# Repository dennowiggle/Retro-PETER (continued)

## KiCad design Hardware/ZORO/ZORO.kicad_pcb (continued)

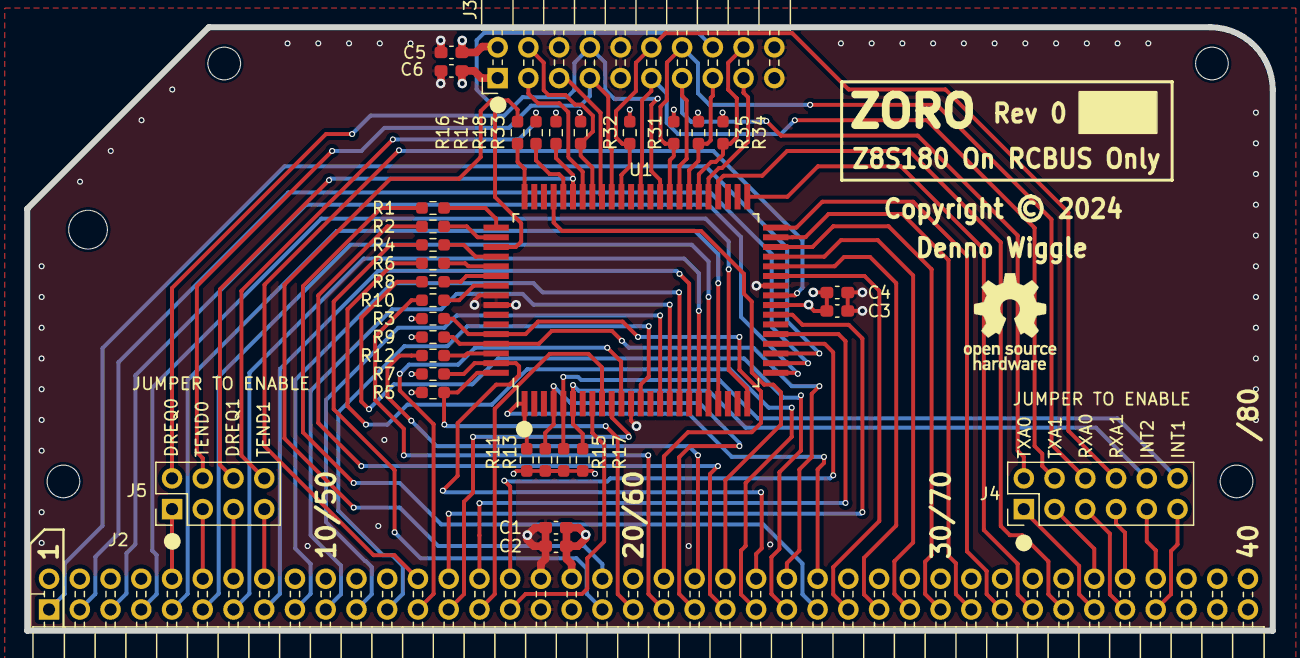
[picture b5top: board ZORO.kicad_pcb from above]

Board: 4 copper layers, 102.9 x 49.9 mm, 41 parts (1 on the bottom side), 81 nets.

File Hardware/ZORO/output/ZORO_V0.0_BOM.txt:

"Reference","Value","Footprint","Qty","DNP","Digikey","Footprint2","LCSC Part #","MPN","Description"
"U1","Z8S18020FSG","WTM_Library:PQFP-80_14x20mm_P0.8mm","1","","269-4541-5-ND","","","Z8S18020FSG","Z8S180 Microprocessor IC Z180 1 Core, 8-Bit 20MHz 80-QFP"
"J2","Conn_02x40_Top_Bottom","WTM_Library:RCBUS_PinHeader_2x40_P2.54mm_Horizontal","1","","A34274-40-ND","","","9-103795-0","CONN HEADER R/A 80POS 2.54MM"
"J3","Conn_02x10_Odd_Even","Connector_PinHeader_2.54mm:PinHeader_2x10_P2.54mm_Horizontal","1","","2057-PH2RA-20-UA-ND","","","PH2RA-20-UA","CONN HEADER HORIZONTAL 20POS 2.54MM"
"J4","Conn_02x06_Odd_Even","Connector_PinHeader_2.54mm:PinHeader_2x06_P2.54mm_Vertical","1","","2057-PH2-12-UA-ND","","","PH2-12-UA","CONN HEADER VERT 12POS 2.54MM"
"J5","Conn_02x04_Odd_Even","Connector_PinHeader_2.54mm:PinHeader_2x04_P2.54mm_Vertical","1","","2057-PH2-08-UA-ND","","","PH2-08-UA","CONN HEADER VERT 8POS 2.54MM"
"R3,R5,R7,R9,R11,R13,R15,R17,R18,R31,R32,R33,R34,R35","10K","Resistor_SMD:R_0603_1608Metric_Pad0.98x0.95mm_HandSolder","14","","311-10.0KHRCT-ND","0603H","C98220","RC0603FR-0710KL","RES 10K OHM 1% 1/10W 0603"
"R1,R2,R4,R6,R8,R10,R12,R14,R16","33R","Resistor_SMD:R_0603_1608Metric_Pad0.98x0.95mm_HandSolder","9","","13-RC0603FR-0733RLCT-ND","0603H","C108661","RC0603FR-0733RL","RES 33 OHM 1% 1/10W 0603"
"C1,C3,C5","4.7uF","Capacitor_SMD:C_0603_1608Metric_Pad1.08x0.95mm_HandSolder","3","","1276-1784-1-ND","0603H","C19666","CL10A475KO8NNNC","CAP CER 4.7UF 16V X5R 0603"
"C2,C4,C6","100nF","Capacitor_SMD:C_0603_1608Metric_Pad1.08x0.95mm_HandSolder","3","","311-1344-1-ND","0603H","C14663","CC0603KRX7R9BB104","CAP CER 0.1UF 50V X7R 0603"

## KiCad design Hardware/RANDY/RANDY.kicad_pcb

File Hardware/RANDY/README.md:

# RANDY
RCBUS Adapter to Nouveau Design. Yeah!

## Description
This project is an adapter board to interface the [2067-Z8S180 board](https://github.com/johnwinans/2067-Z8S180) from John Winan's Z80 Nouveau Project to an RCBUS backplane board connector. 
* If a right-angle RCBUS socket is installed on the top side, the board will plug into an RCBUS expansion port.
* If a right-angle RCBUS plug is installed on the bottom side, the board will plug into an RCBUS card slot.

## Top View

## Bottom View

## RANDY Board Rev 0.0 Release Notes

1. The 'output' directory contains the BOM, netlist, and PDF schematic.

2. Board design used KiCad 8.0.4.

3. J2 changed to Samtec SSW-140-02-F-D-RA.

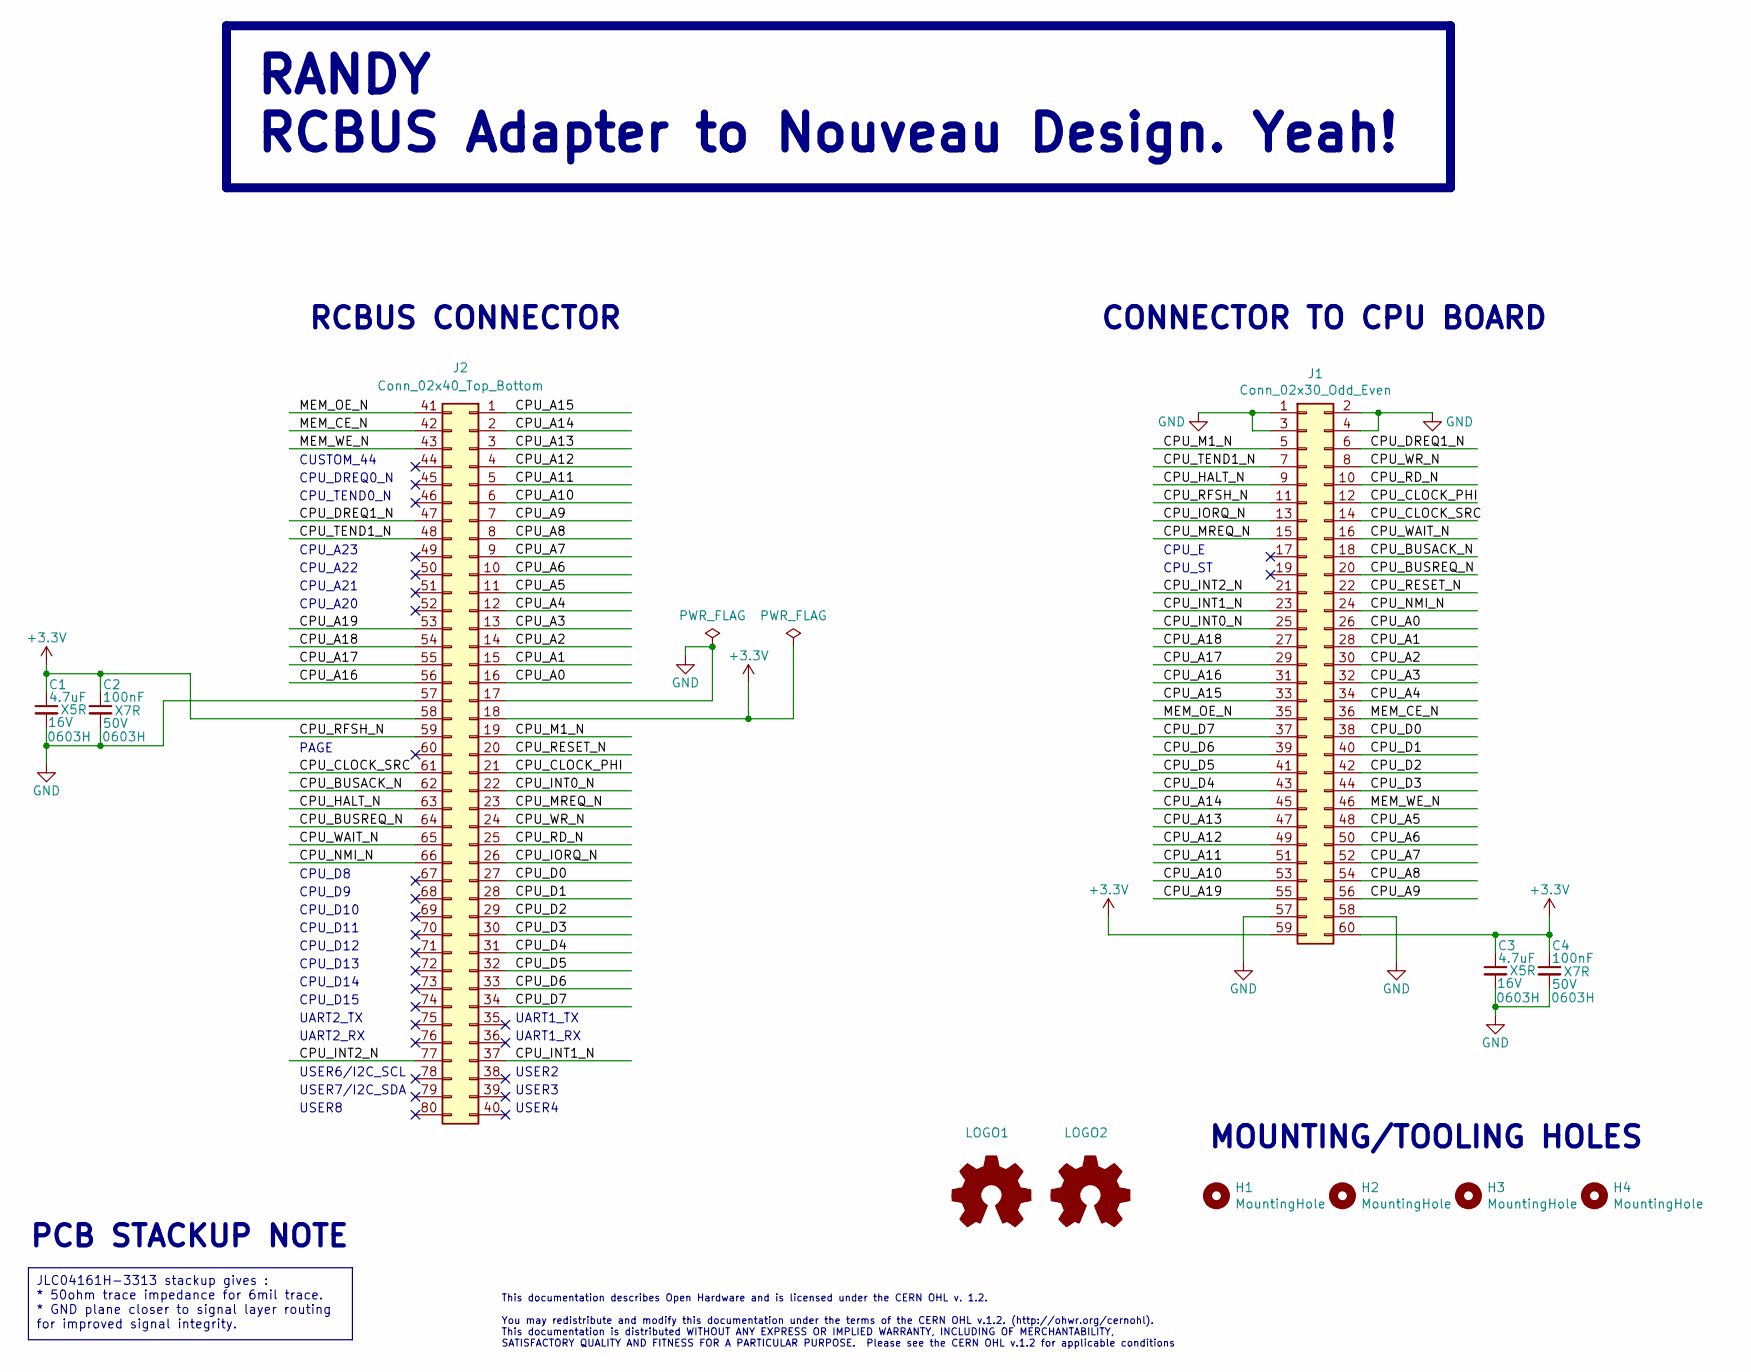
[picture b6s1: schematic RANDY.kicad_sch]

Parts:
C1, C3: 4.7uF; C_0603_1608Metric_Pad1.08x0.95mm_HandSolder; Voltage 16V; Tolerance 10%; MPN CL10A475KO8NNNC; Digikey 1276-1784-1-ND
C2, C4: 100nF; C_0603_1608Metric_Pad1.08x0.95mm_HandSolder; Voltage 50V; Tolerance 10%; MPN CC0603KRX7R9BB104; Digikey 311-1344-1-ND
H1, H2, H3, H4: MountingHole; MountingHole_2.7mm_M2.5_DIN965
J1: Conn_02x30_Odd_Even; PinHeader_2x30_P2.54mm_Vertical; MPN 67996-160HLF; Digikey 609-6334-ND
J2: Conn_02x40_Top_Bottom; PinSocket_2x40_P2.54mm_Horizontal_RCBUS80; MPN SSW-140-02-T-D-RA; Digikey 612-SSW-140-02-T-D-RA-ND
LOGO1, LOGO2: Logo_Open_Hardware_Small; OSHW-Logo_7.5x8mm_SilkScreen

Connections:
+3.3V: C1.1, C2.1, C3.1, C4.1, J1.59, J1.60, J2.18, J2.58
/CPU_A0: J1.26, J2.16
/CPU_A1: J1.28, J2.15
/CPU_A2: J1.30, J2.14
/CPU_A3: J1.32, J2.13
/CPU_A4: J1.34, J2.12
/CPU_A5: J1.48, J2.11
/CPU_A6: J1.50, J2.10
/CPU_A7: J1.52, J2.9
/CPU_A8: J1.54, J2.8
/CPU_A9: J1.56, J2.7
/CPU_A10: J1.53, J2.6
/CPU_A11: J1.51, J2.5
/CPU_A12: J1.49, J2.4
/CPU_A13: J1.47, J2.3
/CPU_A14: J1.45, J2.2
/CPU_A15: J1.33, J2.1
/CPU_A16: J1.31, J2.56
/CPU_A17: J1.29, J2.55
/CPU_A18: J1.27, J2.54
/CPU_A19: J1.55, J2.53
/CPU_BUSACK_N: J1.18, J2.62
/CPU_BUSREQ_N: J1.20, J2.64
/CPU_CLOCK_PHI: J1.12, J2.21
/CPU_CLOCK_SRC: J1.14, J2.61
/CPU_D0: J1.38, J2.27
/CPU_D1: J1.40, J2.28
/CPU_D2: J1.42, J2.29
/CPU_D3: J1.44, J2.30
/CPU_D4: J1.43, J2.31
/CPU_D5: J1.41, J2.32
/CPU_D6: J1.39, J2.33
/CPU_D7: J1.37, J2.34
/CPU_DREQ1_N: J1.6, J2.47
/CPU_HALT_N: J1.9, J2.63
/CPU_INT0_N: J1.25, J2.22
/CPU_INT1_N: J1.23, J2.37
/CPU_INT2_N: J1.21, J2.77
/CPU_IORQ_N: J1.13, J2.26
/CPU_M1_N: J1.5, J2.19
/CPU_MREQ_N: J1.15, J2.23
/CPU_NMI_N: J1.24, J2.66
/CPU_RD_N: J1.10, J2.25
/CPU_RESET_N: J1.22, J2.20
/CPU_RFSH_N: J1.11, J2.59
/CPU_TEND1_N: J1.7, J2.48
/CPU_WAIT_N: J1.16, J2.65
/CPU_WR_N: J1.8, J2.24
/MEM_CE_N: J1.36, J2.42
/MEM_OE_N: J1.35, J2.41
/MEM_WE_N: J1.46, J2.43
GND: C1.2, C2.2, C3.2, C4.2, J1.1, J1.2, J1.3, J1.4, J1.57, J1.58, J2.17, J2.57

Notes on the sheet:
RANDY RCBUS Adapter to Nouveau Design. Yeah!
JLC04161H-3313 stackup gives : * 50ohm trace impedance for 6mil trace. * GND plane closer to signal layer routing for improved signal integrity.
UART1_TX
MOUNTING/TOOLING HOLES
CPU_ST
CONNECTOR TO CPU BOARD
CPU_A22
USER4
CPU_TEND0_N
CPU_D8
CPU_A21
CPU_D11
UART2_RX
CPU_D13
CUSTOM_44
USER6/I2C_SCL
CPU_A23
CPU_D12
PCB STACKUP NOTE
USER8
CPU_E
CPU_D10
CPU_D9
CPU_A20
UART2_TX
CPU_D14
USER3
PAGE
USER2
RCBUS CONNECTOR
CPU_DREQ0_N
This documentation describes Open Hardware and is licensed under the CERN OHL v. 1.2. You may redistribute and modify this documentation under the terms of the CERN OHL v.1.2. (http://ohwr.org/cernohl). This documentation is distributed WITHOUT ANY EXPRESS OR IMPLIED WARRANTY, INCLUDING OF MERCHANT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
USER7/I2C_SDA
CPU_D15
UART1_RX

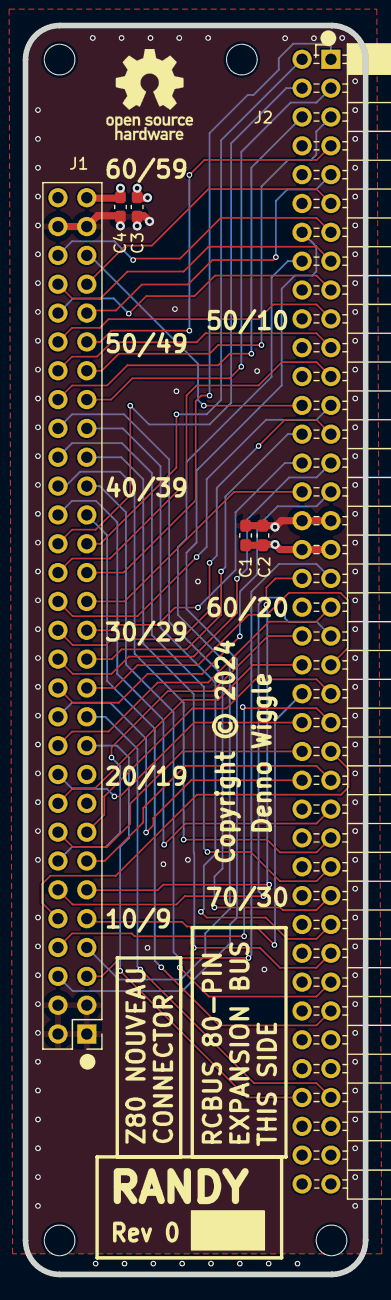
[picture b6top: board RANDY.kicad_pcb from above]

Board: 4 copper layers, 30.0 x 110.0 mm, 12 parts (1 on the bottom side), 52 nets.

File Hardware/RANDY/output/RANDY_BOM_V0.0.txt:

"Reference","Value","Footprint","Qty","DNP","Digikey","LCSC Part #","MPN","Voltage","Description"
"C2,C4","100nF","Capacitor_SMD:C_0603_1608Metric_Pad1.08x0.95mm_HandSolder","2","","311-1344-1-ND","C14663","CC0603KRX7R9BB104","50V","CAP CER 0.1UF 50V X7R 0603"
"C1,C3","4.7uF","Capacitor_SMD:C_0603_1608Metric_Pad1.08x0.95mm_HandSolder","2","","1276-1784-1-ND","C19666","CL10A475KO8NNNC","16V","CAP CER 4.7UF 16V X5R 0603"
"J1","Conn_02x30_Odd_Even","Connector_PinHeader_2.54mm:PinHeader_2x30_P2.54mm_Vertical","1","","609-6334-ND","","67996-160HLF","","CONN HEADER VERT 60POS 2.54MM"
"J2","Conn_02x40_Top_Bottom","WTM_Library:PinSocket_2x40_P2.54mm_Horizontal_RCBUS80","1","","612-SSW-140-02-T-D-RA-ND","","SSW-140-02-T-D-RA","","CONN RCPT 80POS 0.1 TIN PCB R/A"

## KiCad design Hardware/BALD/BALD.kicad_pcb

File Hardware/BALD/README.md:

# BALD
Bus Activity LED Display.

## Description
BALD is an RCBUS board with LED's to show bus activity.

## Top View

## Bottom View

## BALD Board Rev 0.0 Release Notes

1. The 'output' directory contains the BOM, netlist, and PDF schematic.

2. Board design used KiCad 8.0.4.

3. J1 was changed to Adam Tech part number PH2RA-80-UA to reduce insertion force.

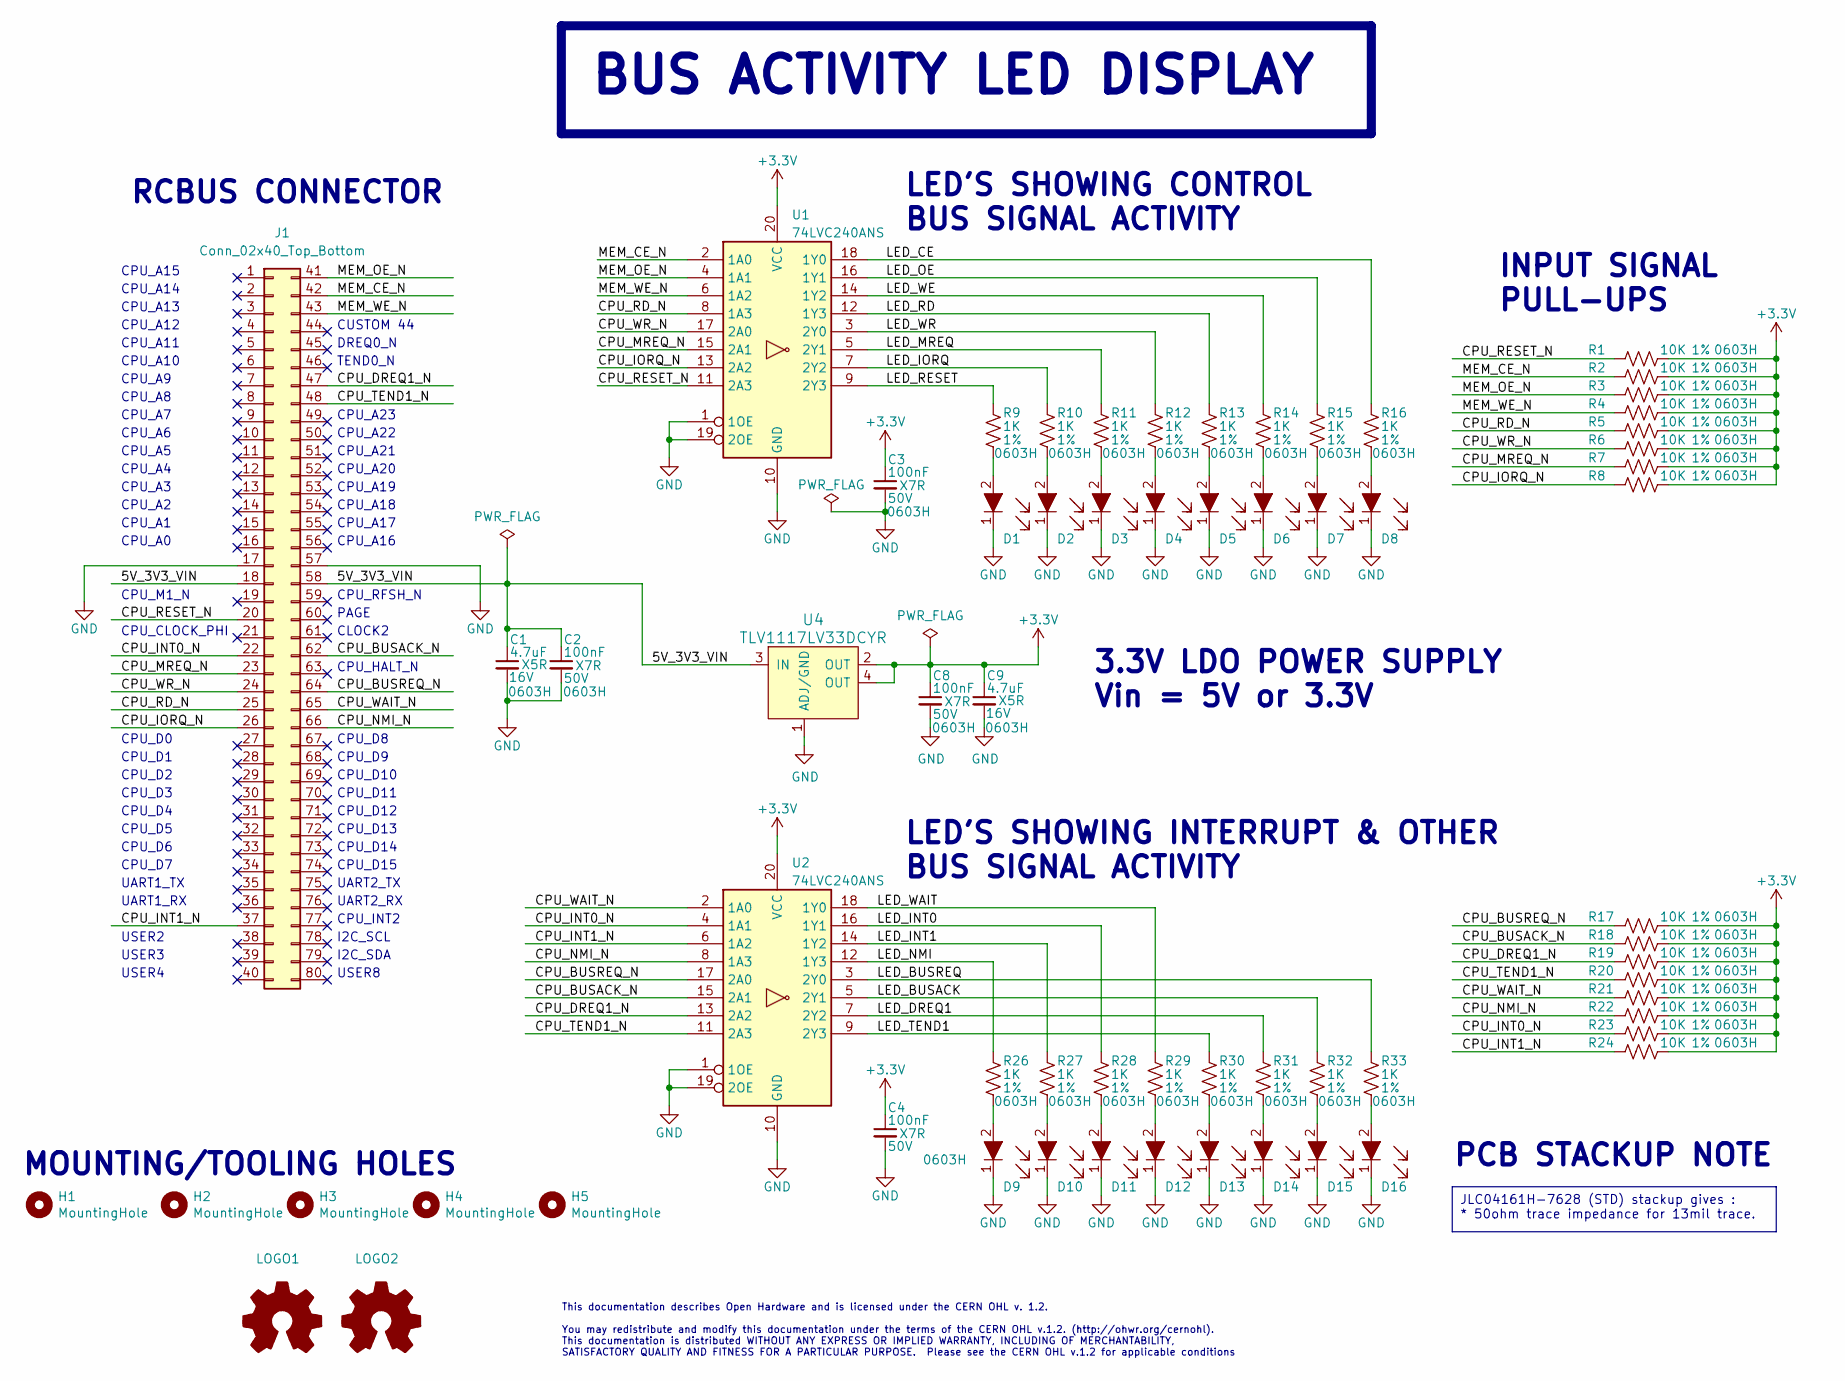
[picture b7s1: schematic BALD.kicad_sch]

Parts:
C1, C9: 4.7uF; C_0603_1608Metric_Pad1.08x0.95mm_HandSolder; Voltage 16V; Tolerance 10%; MPN CL10A475KO8NNNC; Digikey 1276-1784-1-ND
C2, C3, C4, C8: 100nF; C_0603_1608Metric_Pad1.08x0.95mm_HandSolder; Voltage 50V; Tolerance 10%; MPN CC0603KRX7R9BB104; Digikey 311-1344-1-ND
D1, D2, D3, D4, D5, D6, D7, D8, D9, D10, D11, D12, D13, D14, D15, D16: LED_LTST-S270KGKT; LTST-S270KGKT; MPN LTST-S270KGKT; Digikey 160-1478-1-ND
H1: MountingHole; MountingHole_3.2mm_M3
H2, H3, H4, H5: MountingHole; MountingHole_2.7mm_M2.5_DIN965
J1: Conn_02x40_Top_Bottom; RCBUS_PinHeader_2x40_P2.54mm_Horizontal; MPN 9-103795-0; Digikey A34274-40-ND
LOGO1, LOGO2: Logo_Open_Hardware_Small; OSHW-Logo_7.5x8mm_SilkScreen
R1, R2, R3, R4, R5, R6, R7, R8, R17, R18, R19, R20, R21, R22, R23, R24: 10K; R_0603_1608Metric_Pad0.98x0.95mm_HandSolder; Tolerance 1%; MPN RC0603FR-0710KL; Digikey 311-10.0KHRCT-ND
R9, R10, R11, R12, R13, R14, R15, R16, R26, R27, R28, R29, R30, R31, R32, R33: 1K; R_0603_1608Metric_Pad0.98x0.95mm_HandSolder; Tolerance 1%; MPN RC0603FR-071KL; Digikey 311-1.00KHRCT-ND
U1, U2: 74LVC240ANS; SO-20_5.3x12.6mm_P1.27mm; MPN SN74LVC240ANS; Digikey 296-53353-ND
U4: TLV1117LV33DCYR; SOT-223; MPN TLV1117LV33DCYR; Digikey 296-28778-1-ND

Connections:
+3.3V: C3.1, C4.1, C8.1, C9.1, R1.2, R2.2, R3.2, R4.2, R5.2, R6.2, R7.2, R8.2, R17.2, R18.2, R19.2, R20.2, R21.2, R22.2, R23.2, R24.2, U1.20 (VCC), U2.20 (VCC), U4.2 (OUT), U4.4 (OUT)
/5V_3V3_VIN: C1.1, C2.1, J1.18, J1.58, U4.3 (IN)
/CPU_BUSACK_N: J1.62, R18.1, U2.15 (2A1)
/CPU_BUSREQ_N: J1.64, R17.1, U2.17 (2A0)
/CPU_DREQ1_N: J1.47, R19.1, U2.13 (2A2)
/CPU_INT0_N: J1.22, R23.1, U2.4 (1A1)
/CPU_INT1_N: J1.37, R24.1, U2.6 (1A2)
/CPU_IORQ_N: J1.26, R8.1, U1.13 (2A2)
/CPU_MREQ_N: J1.23, R7.1, U1.15 (2A1)
/CPU_NMI_N: J1.66, R22.1, U2.8 (1A3)
/CPU_RD_N: J1.25, R5.1, U1.8 (1A3)
/CPU_RESET_N: J1.20, R1.1, U1.11 (2A3)
/CPU_TEND1_N: J1.48, R20.1, U2.11 (2A3)
/CPU_WAIT_N: J1.65, R21.1, U2.2 (1A0)
/CPU_WR_N: J1.24, R6.1, U1.17 (2A0)
/LED_BUSACK: R32.1, U2.5 (2Y1)
/LED_BUSREQ: R33.1, U2.3 (2Y0)
/LED_CE: R16.1, U1.18 (1Y0)
/LED_DREQ1: R31.1, U2.7 (2Y2)
/LED_INT0: R28.1, U2.16 (1Y1)
/LED_INT1: R27.1, U2.14 (1Y2)
/LED_IORQ: R10.1, U1.7 (2Y2)
/LED_MREQ: R11.1, U1.5 (2Y1)
/LED_NMI: R26.1, U2.12 (1Y3)
/LED_OE: R15.1, U1.16 (1Y1)
/LED_RD: R13.1, U1.12 (1Y3)
/LED_RESET: R9.1, U1.9 (2Y3)
/LED_TEND1: R30.1, U2.9 (2Y3)
/LED_WAIT: R29.1, U2.18 (1Y0)
/LED_WE: R14.1, U1.14 (1Y2)
/LED_WR: R12.1, U1.3 (2Y0)
/MEM_CE_N: J1.42, R2.1, U1.2 (1A0)
/MEM_OE_N: J1.41, R3.1, U1.4 (1A1)
/MEM_WE_N: J1.43, R4.1, U1.6 (1A2)
GND: C1.2, C2.2, C3.2, C4.2, C8.2, C9.2, D1.1, D2.1, D3.1, D4.1, D5.1, D6.1, D7.1, D8.1, D9.1, D10.1, D11.1, D12.1, D13.1, D14.1, D15.1, D16.1, J1.17, J1.57, U1.1 (1OE), U1.10 (GND), U1.19 (2OE), U2.1 (1OE), U2.10 (GND), U2.19 (2OE), U4.1 (ADJ/GND)
unnamed: D1.2, R9.2
unnamed: D2.2, R10.2
unnamed: D3.2, R11.2
unnamed: D4.2, R12.2
unnamed: D5.2, R13.2
unnamed: D6.2, R14.2
unnamed: D7.2, R15.2
unnamed: D8.2, R16.2
unnamed: D9.2, R26.2
unnamed: D10.2, R27.2
unnamed: D11.2, R28.2
unnamed: D12.2, R29.2
unnamed: D13.2, R30.2
unnamed: D14.2, R31.2
unnamed: D15.2, R32.2
unnamed: D16.2, R33.2

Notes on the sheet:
BUS ACTIVITY LED DISPLAY
JLC04161H-7628 (STD) stackup gives : * 50ohm trace impedance for 13mil trace.
I2C_SDA
CPU_D3
CPU_A17
USER3
CPU_A11
CPU_A8
CPU_D14
CPU_A18
RCBUS CONNECTOR
CPU_A6
UART1_RX
CPU_A7
CPU_D4
CPU_D2
CPU_A14
CPU_D6
CPU_D13
CUSTOM 44
CPU_A3
CPU_A9
CPU_A15
CPU_A19
DREQ0_N
CPU_CLOCK_PHI
CPU_D12
CPU_A10
CPU_A23
CPU_A16
INPUT SIGNAL PULL-UPS
CPU_D11
CPU_A5
CPU_D9
CPU_D7
TEND0_N
LED'S SHOWING CONTROL BUS SIGNAL ACTIVITY
USER8
CPU_A13
CPU_D0

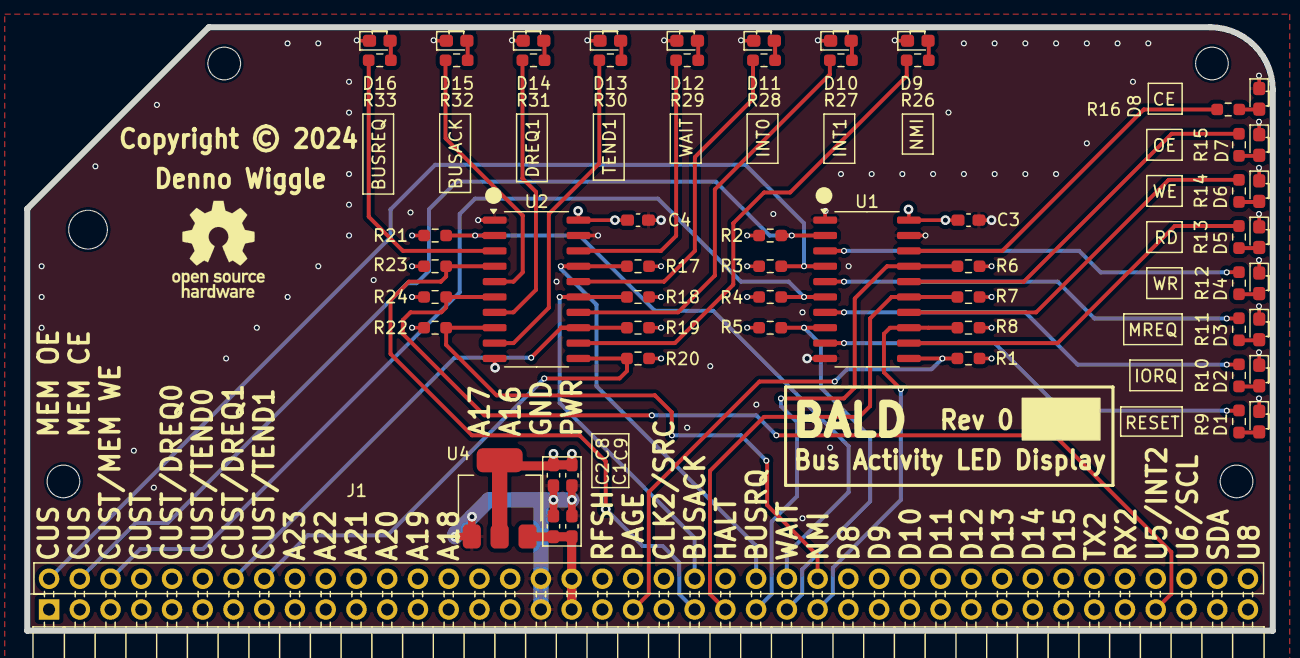
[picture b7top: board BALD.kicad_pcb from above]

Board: 4 copper layers, 102.9 x 49.9 mm, 65 parts (1 on the bottom side), 51 nets.

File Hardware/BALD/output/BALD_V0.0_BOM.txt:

"Reference","Value","Footprint","Qty","DNP","Digikey","Footprint2","LCSC Part #","MPN","Manufacturer","Voltage","Description","Manufactutrer"
"U4","TLV1117LV33DCYR","Package_TO_SOT_SMD:SOT-223","1","","296-28778-1-ND","","C15578","TLV1117LV33DCYR","Texas Instruments","","IC REG LINEAR 3.3V 1A SOT223-4",""
"U1,U2","74LVC240ANS","Package_SO:SO-20_5.3x12.6mm_P1.27mm","2","","296-53353-ND","","","SN74LVC240ANS","Texas Instruments","","IC BUFFER INVERT 3.6V 20SO",""
"R9,R10,R11,R12,R13,R14,R15,R16,R26,R27,R28,R29,R30,R31,R32,R33","1K","Resistor_SMD:R_0603_1608Metric_Pad0.98x0.95mm_HandSolder","16","","311-1.00KHRCT-ND","0603H","C22548","RC0603FR-071KL","Yaego","","RES 1K OHM 1% 1/10W 0603",""
"R1,R2,R3,R4,R5,R6,R7,R8,R17,R18,R19,R20,R21,R22,R23,R24","10K","Resistor_SMD:R_0603_1608Metric_Pad0.98x0.95mm_HandSolder","16","","311-10.0KHRCT-ND","0603H","C98220","RC0603FR-0710KL","Yaego","","RES 10K OHM 1% 1/10W 0603",""
"J1","Conn_02x40_Top_Bottom","WTM_Library:RCBUS_PinHeader_2x40_P2.54mm_Horizontal","1","","A34274-40-ND","","","9-103795-0","TE Connectivity AMP Connectors","","CONN HEADER R/A 80POS 2.54MM",""
"D1,D2,D3,D4,D5,D6,D7,D8,D9,D10,D11,D12,D13,D14,D15,D16","LED_LTST-S270KGKT","WTM_Library:LTST-S270KGKT","16","","160-1478-1-ND","","C125113","LTST-S270KGKT","Lite-On Inc.","","LED 571NM GREEN CLEAR CHIP 0603 R/A",""
"C2,C3,C4,C8","100nF","Capacitor_SMD:C_0603_1608Metric_Pad1.08x0.95mm_HandSolder","4","","311-1344-1-ND","0603H","C14663","CC0603KRX7R9BB104","YAGEO","50V","CAP CER 0.1UF 50V X7R 0603",""
"C1,C9","4.7uF","Capacitor_SMD:C_0603_1608Metric_Pad1.08x0.95mm_HandSolder","2","","1276-1784-1-ND","0603H","C19666","CL10A475KO8NNNC","Yaego","16V","CAP CER 4.7UF 16V X5R 0603",""

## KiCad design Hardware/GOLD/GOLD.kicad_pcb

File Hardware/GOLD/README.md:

# GOLD
GPIO On LED Display

## Description
GOLD is a small breakout board that connects to the GPIO connector on PETER to display signal status on 6 LED's.

## Top View

## Bottom View

## GOLD Board Rev 0.0 Release Notes

1. The 'output' directory contains the BOM, netlist, and PDF schematic.

2. Board design used KiCad 8.0.4.

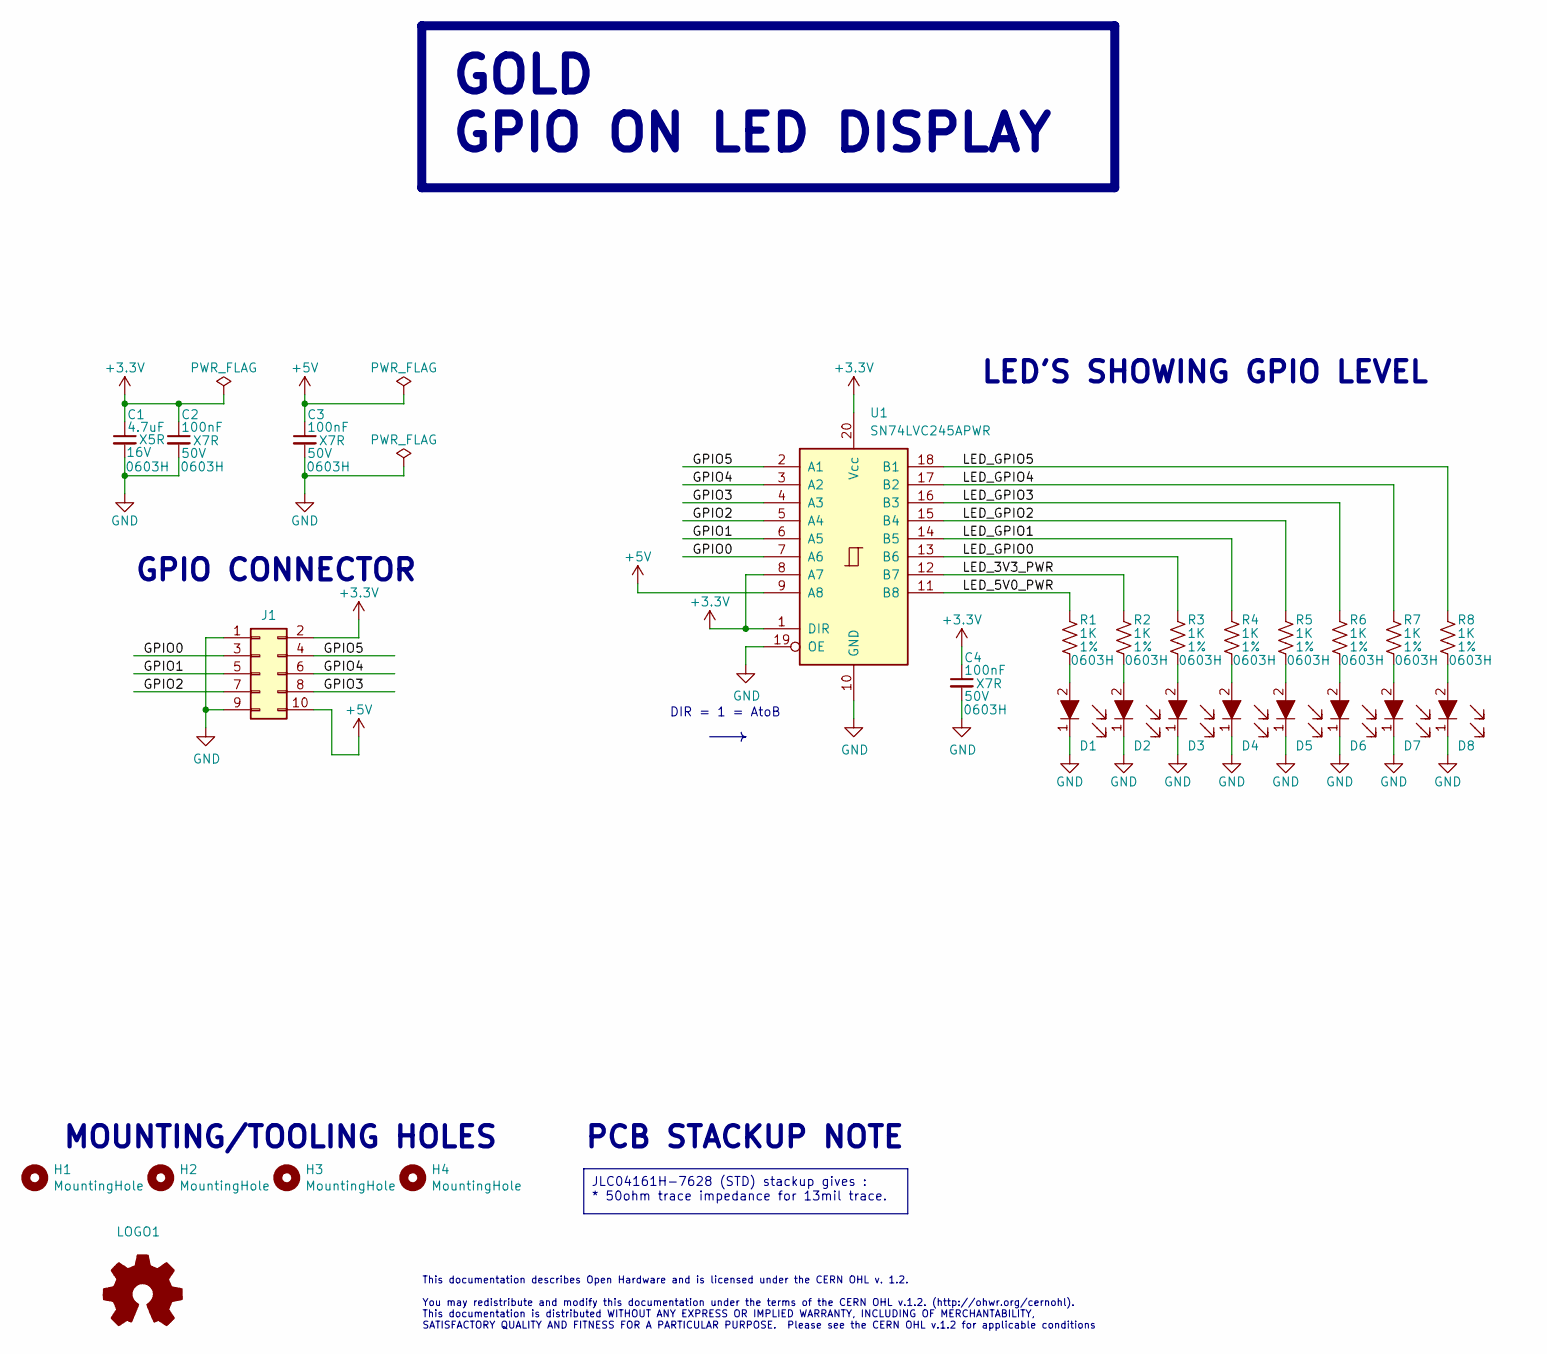
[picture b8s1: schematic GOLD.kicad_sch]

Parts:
C1: 4.7uF; C_0603_1608Metric_Pad1.08x0.95mm_HandSolder; Voltage 16V; Tolerance 10%; MPN CL10A475KO8NNNC; Digikey 1276-1784-1-ND
C2, C3, C4: 100nF; C_0603_1608Metric_Pad1.08x0.95mm_HandSolder; Voltage 50V; Tolerance 10%; MPN CC0603KRX7R9BB104; Digikey 311-1344-1-ND
D1, D2, D3, D4, D5, D6, D7, D8: LED_LTST-S270KGKT; LTST-S270KGKT; MPN LTST-S270KGKT; Digikey 160-1478-1-ND
H1, H2, H3, H4: MountingHole; MountingHole_2.7mm_M2.5_DIN965
J1: Conn_02x05_Vertical; PinSocket_2x05_P2.54mm_Vertical; MPN 61301021821; Digikey 732-2861-ND
LOGO1: Logo_Open_Hardware_Small; OSHW-Logo_7.5x8mm_SilkScreen
R1, R2, R3, R4, R5, R6, R7, R8: 1K; R_0603_1608Metric_Pad0.98x0.95mm_HandSolder; Tolerance 1%; MPN RC0603FR-071KL; Digikey 311-1.00KHRCT-ND
U1: SN74LVC245APWR; TSSOP-20_4.4x6.5mm_P0.65mm; MPN SN74LVC245APWR; Digikey 296-1233-1-ND

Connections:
+3.3V: C1.1, C2.1, C4.1, J1.2, U1.1 (DIR), U1.8 (A7), U1.20 (Vcc)
+5V: C3.1, J1.10, U1.9 (A8)
/GPIO0: J1.3, U1.7 (A6)
/GPIO1: J1.5, U1.6 (A5)
/GPIO2: J1.7, U1.5 (A4)
/GPIO3: J1.8, U1.4 (A3)
/GPIO4: J1.6, U1.3 (A2)
/GPIO5: J1.4, U1.2 (A1)
/LED_3V3_PWR: R2.1, U1.12 (B7)
/LED_5V0_PWR: R1.1, U1.11 (B8)
/LED_GPIO0: R3.1, U1.13 (B6)
/LED_GPIO1: R4.1, U1.14 (B5)
/LED_GPIO2: R5.1, U1.15 (B4)
/LED_GPIO3: R6.1, U1.16 (B3)
/LED_GPIO4: R7.1, U1.17 (B2)
/LED_GPIO5: R8.1, U1.18 (B1)
GND: C1.2, C2.2, C3.2, C4.2, D1.1, D2.1, D3.1, D4.1, D5.1, D6.1, D7.1, D8.1, J1.1, J1.9, U1.10 (GND), U1.19 (OE)
unnamed: D1.2, R1.2
unnamed: D2.2, R2.2
unnamed: D3.2, R3.2
unnamed: D4.2, R4.2
unnamed: D5.2, R5.2
unnamed: D6.2, R6.2
unnamed: D7.2, R7.2
unnamed: D8.2, R8.2

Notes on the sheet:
GOLD GPIO ON LED DISPLAY
JLC04161H-7628 (STD) stackup gives : * 50ohm trace impedance for 13mil trace.
PCB STACKUP NOTE
GPIO CONNECTOR
DIR = 1 = AtoB
LED'S SHOWING GPIO LEVEL
MOUNTING/TOOLING HOLES
This documentation describes Open Hardware and is licensed under the CERN OHL v. 1.2. You may redistribute and modify this documentation under the terms of the CERN OHL v.1.2. (http://ohwr.org/cernohl). This documentation is distributed WITHOUT ANY EXPRESS OR IMPLIED WARRANTY, INCLUDING OF MERCHANT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

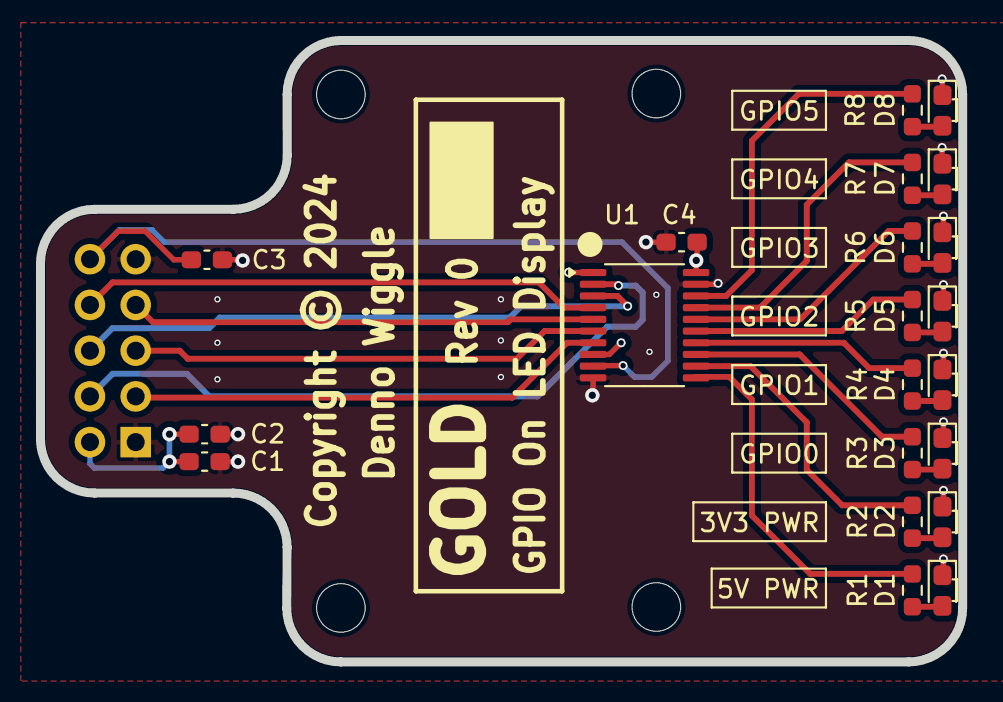
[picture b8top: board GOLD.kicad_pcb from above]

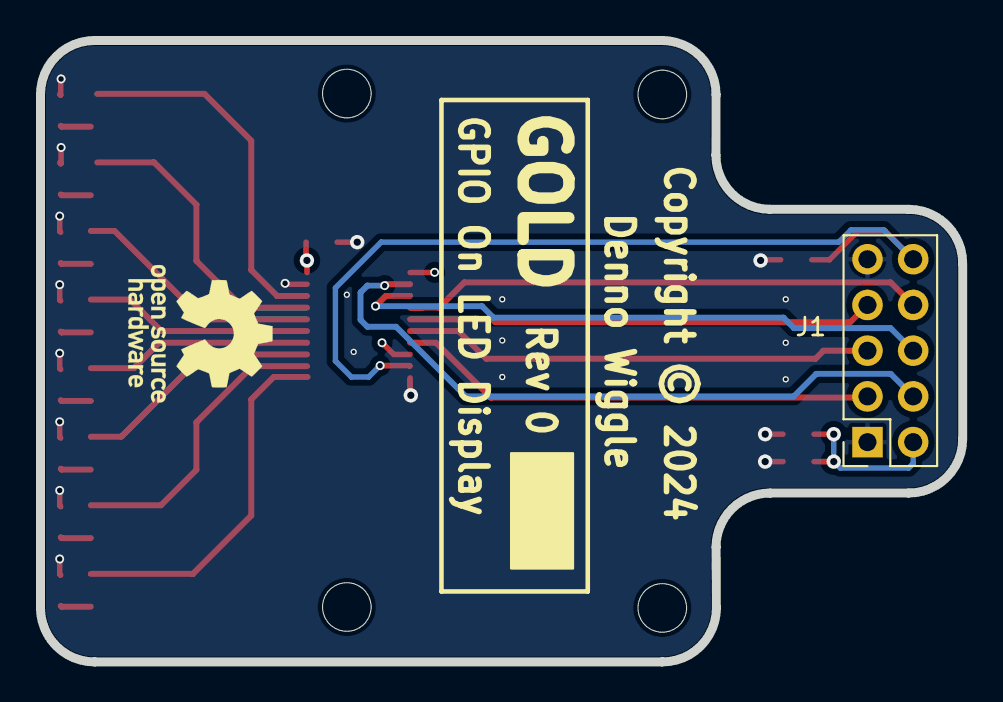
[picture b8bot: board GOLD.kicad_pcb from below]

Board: 4 copper layers, 51.2 x 34.5 mm, 27 parts (2 on the bottom side), 25 nets.

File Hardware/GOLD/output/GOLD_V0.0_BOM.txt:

"Reference","Value","Footprint","Qty","DNP","Digikey","Footprint2","LCSC Part #","MPN","Voltage","Description"
"U1","SN74LVC245APWR","Package_SO:TSSOP-20_4.4x6.5mm_P0.65mm","1","","296-1233-1-ND","","C7848","SN74LVC245APWR","","IC TXRX NON-INVERT 3.6V 20TSSOP"
"D1,D2,D3,D4,D5,D6,D7,D8","LED_LTST-S270KGKT","WTM_Library:LTST-S270KGKT","8","","160-1478-1-ND","","C125113","LTST-S270KGKT","","LED 571NM GREEN CLEAR CHIP 0603 R/A"
"J1","Conn_02x05_Vertical","Connector_PinSocket_2.54mm:PinSocket_2x05_P2.54mm_Vertical","1","","732-2861-ND","","","61301021821","","CONN HDR 10POS 0.1 GOLD PCB"
"R1,R2,R3,R4,R5,R6,R7,R8","1K","Resistor_SMD:R_0603_1608Metric_Pad0.98x0.95mm_HandSolder","8","","311-1.00KHRCT-ND","0603H","C22548","RC0603FR-071KL","","RES 1K OHM 1% 1/10W 0603"
"C1","4.7uF","Capacitor_SMD:C_0603_1608Metric_Pad1.08x0.95mm_HandSolder","1","","1276-1784-1-ND","0603H","C19666","CL10A475KO8NNNC","16V","CAP CER 4.7UF 16V X5R 0603"
"C2,C3,C4","100nF","Capacitor_SMD:C_0603_1608Metric_Pad1.08x0.95mm_HandSolder","3","","311-1344-1-ND","0603H","C14663","CC0603KRX7R9BB104","50V","CAP CER 0.1UF 50V X7R 0603"

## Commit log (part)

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2024-08-28 Initial Commit of PETER
2024-08-28 Update Readme files.
2024-08-28 Update Readme and License files.
2024-08-28 Update Readme files
2024-08-28 Update Readme file.
2024-08-29 Update Readme files. Add the GOLD board hardware design files.
2024-08-29 Update Readme file
2024-08-30 Initial commit of BALD board.
2024-08-31 Initial Commit Randy
2024-08-31 Upddate Readme file
2024-09-01 Initial commit of the ZORO board.
2024-09-02 Initial commit of the SEWER card.
2026-05-19 Initial release of ANALYZER
2026-05-19 Doc update.
2026-05-19 Initial release of SPIFEE
2026-05-19 Initial release of BUTLER
2026-05-19 Correct typo.
